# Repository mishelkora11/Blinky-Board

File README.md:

# Blinky-Board

Video showing the Blinky Board works: 
https://jumpshare.com/share/0ToqgzvF8R0nfnmqCSlf

PCB in 3D viewer:

PCB in Kicad:

Schematic in Kicad:

Blinky Board Assembled:

BOM:
[BOM.csv](https://github.com/user-attachments/files/31109765/BOM.csv)

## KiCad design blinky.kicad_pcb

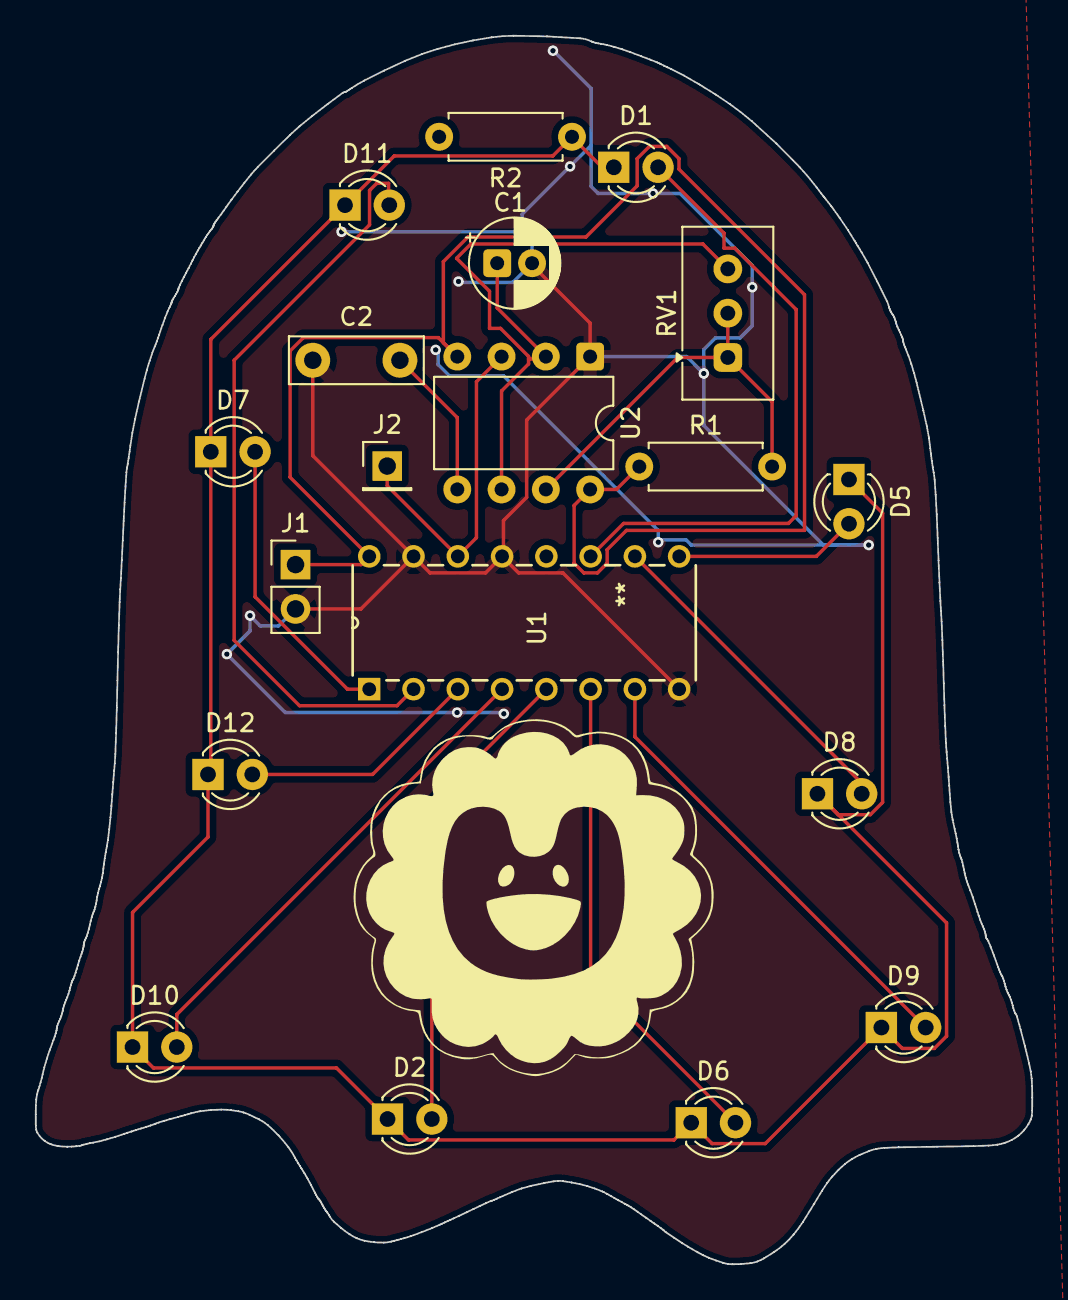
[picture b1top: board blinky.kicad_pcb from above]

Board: 2 copper layers, 57.2 x 70.5 mm, 19 parts (0 on the bottom side), 17 nets.

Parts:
C1: C_Polarized; CP_Radial_D5.0mm_P2.00mm
C2: C; C_Disc_D7.5mm_W2.5mm_P5.00mm
D1, D2, D5, D6, D7, D8, D9, D10, D11, D12: LED; LED_D3.0mm
J1: Conn_01x02_Socket; PinHeader_1x02_P2.54mm_Vertical
J2: Conn_01x01_Socket; PinHeader_1x01_P2.54mm_Vertical
R1: 1k; R_Axial_DIN0207_L6.3mm_D2.5mm_P7.62mm_Horizontal
R2: 470; R_Axial_DIN0207_L6.3mm_D2.5mm_P7.62mm_Horizontal
RV1: 50k; Potentiometer_Vishay_T93YA_Vertical
U1: 4017; cd4017
U2: NE555P; DIP-8_W7.62mm

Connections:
+5V: J1.1, R1.1, U1.16 (VDD), U2.4 (~RST), U2.8 (VCC)
GND: C1.2, C2.1, J1.2, U1.8 (VSS), U1.13 (CKEN), U1.15 (Reset), U2.1 (GND)
unnamed: D1.2 (A), U1.11 (Q9)
unnamed: D1.1 (K), D2.1 (K), D5.1 (K), D6.1 (K), D7.1 (K), D8.1 (K), D9.1 (K), D10.1 (K), D11.1 (K), D12.1 (K), R2.1
unnamed: D2.2 (A), U1.5 (Q6)
unnamed: D5.2 (A), U1.9 (Q8)
unnamed: D6.2 (A), U1.6 (Q7)
unnamed: D7.2 (A), U1.1 (Q5)
unnamed: D8.2 (A), U1.10 (Q4)
unnamed: D9.2 (A), U1.7 (Q3)
unnamed: D10.2 (A), U1.4 (Q2)
unnamed: D11.2 (A), U1.2 (Q1)
unnamed: D12.2 (A), U1.3 (Q0)
unnamed: C2.2, U2.5 (CONT)
unnamed: R1.2, RV1.1, RV1.2, U2.7 (DISCH)
OUT: J2.1 (Pin_1_1), U1.14 (CLK), U2.3 (OUT)
TR: C1.1, RV1.3, U2.2 (TRIG), U2.6 (THRES)
